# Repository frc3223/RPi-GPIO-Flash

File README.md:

# Ring-light-flash
What does this do?

This is a small Python program meant for a Raspberry Pi 3B running Raspbian Buster Lite, and utilizing Python 2.7. The premise behind it is to control a 12v 100mA Ring Light over GPIO by sending a signal to a Transistor using GPIO Pin 12 (GPIO_18)

Ideally, this program is meant for FRC vision development using a open source vision application like Chameleon Vision. The design of the coprocessor is up to you, but this application is just meant for giving you control over the state of the ring light.

Made by Colin Gideon "SpookyWoogin", FRC 3223, Robotics of Central Kitsap

Copyright 2019, protected under the GNU General Public Licence.
This design has been depricated in pursuit of a better design.

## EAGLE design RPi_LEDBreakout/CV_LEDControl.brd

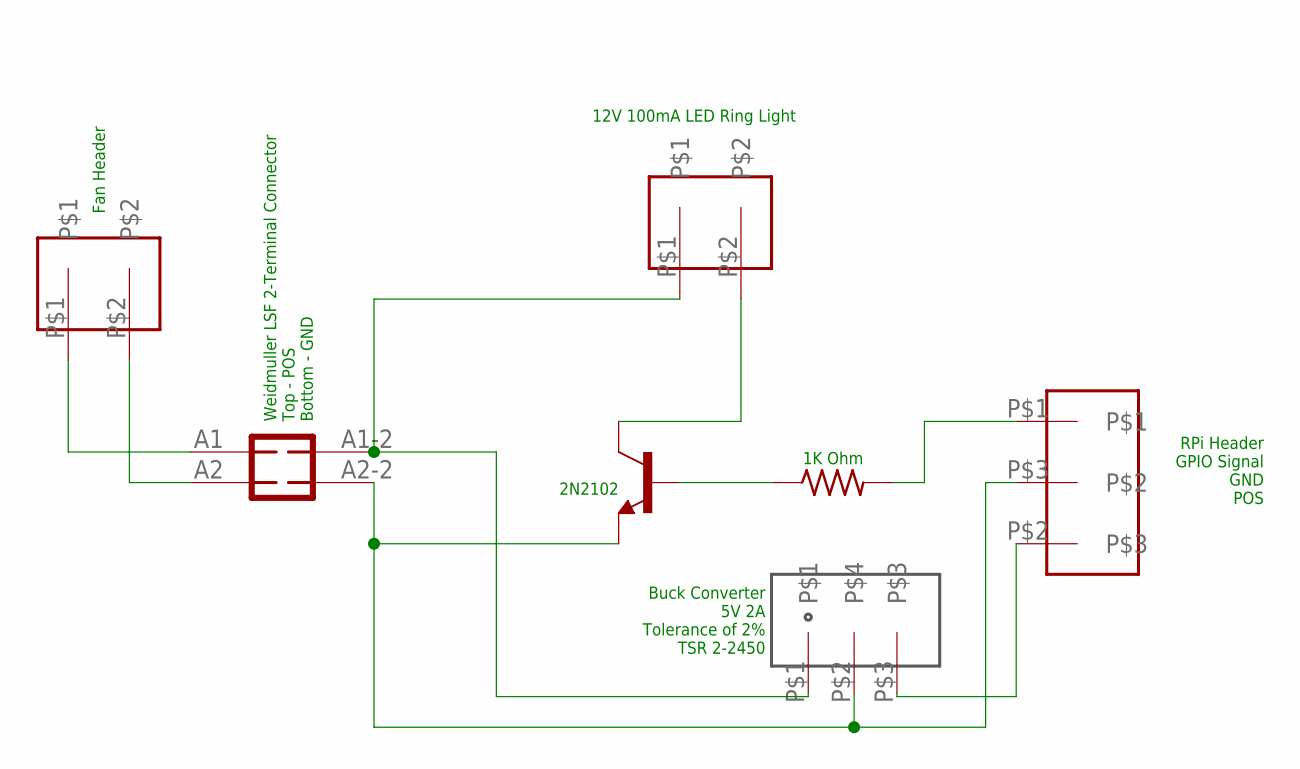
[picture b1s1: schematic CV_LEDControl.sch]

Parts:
R1: R-US_0204/7; 0204/7
T1: 2N2102; TO5
U$1: TSR2-2450; TSR2
U$2: 2-PORTTERMINAL-26AWG
U$3: 2-PORTTERMINAL-22AWG
U$4: 3-PORTTERMINAL-22AWG
WEIDMULLERLSF: WEIDMUELLER_1824420000WEIDMUELLER_1824420000_0_0; WEIDMUELLER_1824420000_0

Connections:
unnamed: U$2.P$1, WEIDMULLERLSF.A1 (A4)
unnamed: U$2.P$2, WEIDMULLERLSF.A2 (A3)
unnamed: U$1.P$1, U$3.P$1, WEIDMULLERLSF.A1-2 (A1)
unnamed: T1.3 (C), U$3.P$2
unnamed: R1.2, U$4.P$1
unnamed: R1.1, T1.2 (B)
unnamed: T1.1 (E), U$1.P$2, U$4.P$3, WEIDMULLERLSF.A2-2 (A2)
unnamed: U$1.P$3, U$4.P$2

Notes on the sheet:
Weidmuller LSF 2-Terminal Connector Top - POS Bottom - GND
Fan Header
RPi Header GPIO Signal GND POS
Buck Converter 5V 2A Tolerance of 2% TSR 2-2450
2N2102
1K Ohm
12V 100mA LED Ring Light

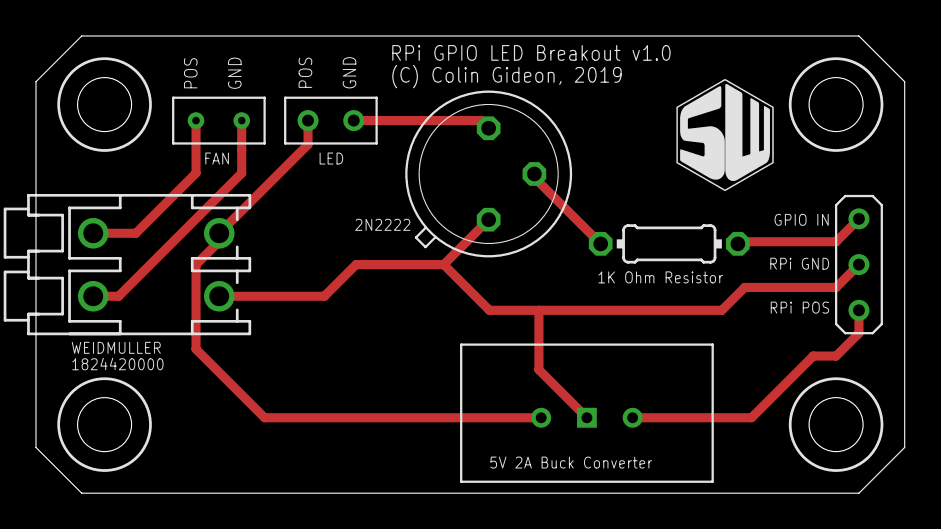
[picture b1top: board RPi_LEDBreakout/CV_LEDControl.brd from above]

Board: 2 copper layers, 48.3 x 25.4 mm, 7 parts (0 on the bottom side), 8 nets.

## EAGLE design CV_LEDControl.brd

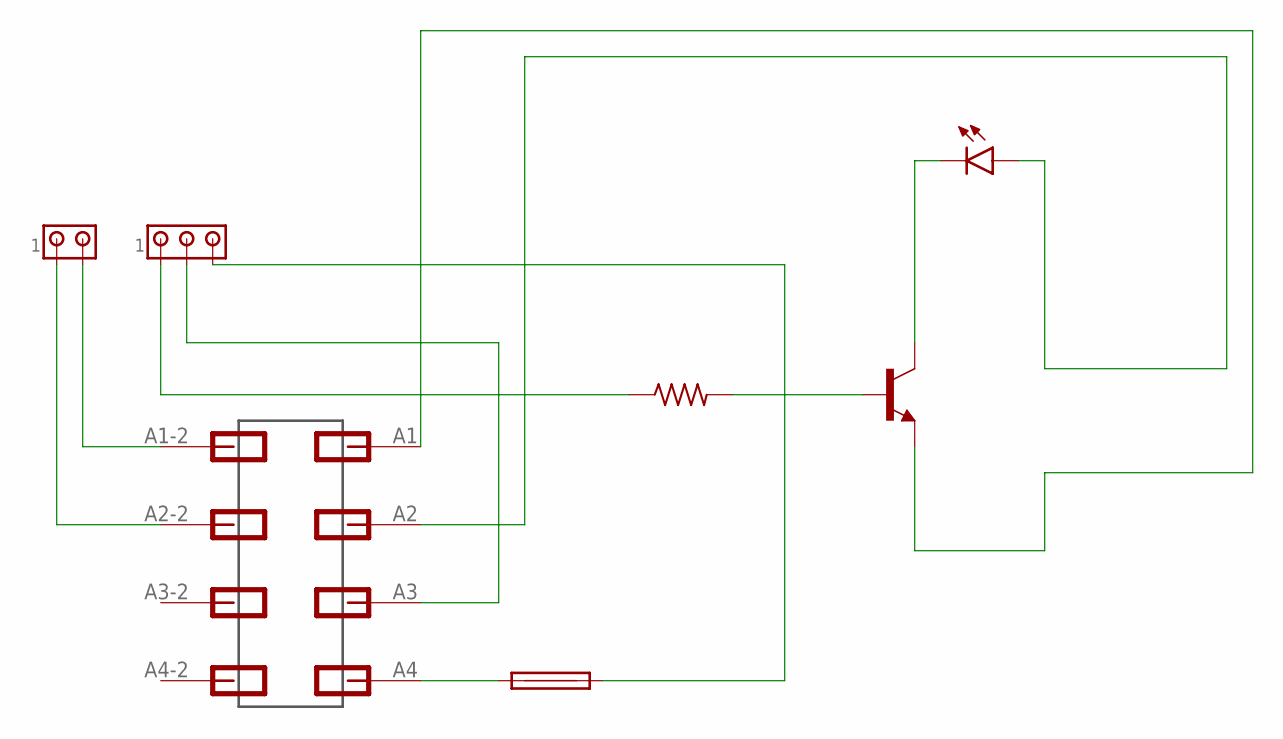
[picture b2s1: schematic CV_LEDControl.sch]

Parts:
E1: WEIDMUELLER_1824440000WEIDMUELLER_1824440000_0_0; WEIDMUELLER_1824440000_0
F1: SH22,5
J1: MTA03-100; 10X03MTA
J2: MTA02-100; 10X02MTA
LED1: LED3MM
R1: R-US_0204/7; 0204/7
T1: 2N2102; TO5

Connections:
unnamed: R1.2, T1.2 (B)
unnamed: J1.1, R1.1
unnamed: E1.A4 (A3), F1.1
unnamed: LED1.K (C), T1.3 (C)
unnamed: E1.A2 (A1), LED1.A
unnamed: F1.2, J1.3
unnamed: E1.A3 (A2), J1.2
unnamed: E1.A2-2 (A6), J2.1
unnamed: E1.A1-2 (A5), J2.2
unnamed: E1.A1 (A4), T1.1 (E)

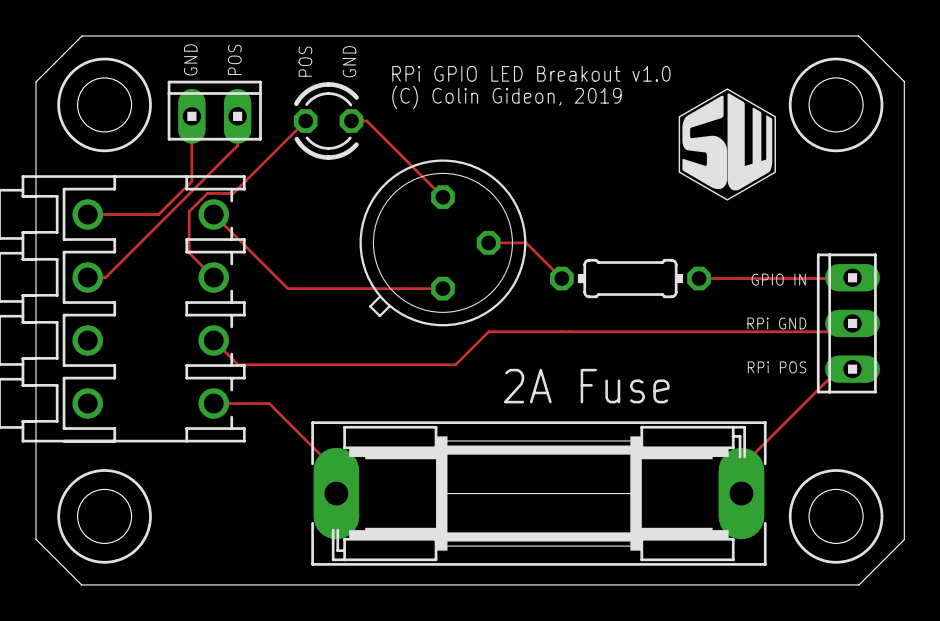
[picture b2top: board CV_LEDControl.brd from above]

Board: 2 copper layers, 48.2 x 30.5 mm, 7 parts (0 on the bottom side), 10 nets.

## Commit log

2019-12-06 Addition of code
2019-12-06 Added credits at top
2019-12-09 Cleaned up the code, now its smol
2019-12-10 Forgot a delay after the light toggles off
2019-12-11 Adjusted formatting on README
2019-12-17 Addition of Hardware-side component files
    Includes the Gerber files for a pre-generated version of the board, and the EAGLE files for easy editing. Is this enough to clear me from R16 though...? :thonkang:
2019-12-17 Updated files to fix hole spacing and RPi output layout
2019-12-24 Redid board layout to terminate 5V line input
2020-01-05 Updated board design and added cleanup to end behavior
2020-01-05 Stripped out all board files except for board schematic
2020-01-05 Sped up timing and simplified Yes/No prompts
2020-01-17 Adding pyNT, yayyy
2020-01-17 Network Switch is working! RIP Command line switch. You will be missed...
2020-01-17 Merge changes from Dev
    * Adding pyNT, yayyy
    * Network Switch is working! RIP Command line switch. You will be missed...
2020-01-17 Removed IP
2020-01-17 Trying to revive the terminal switch as a LED lockout
